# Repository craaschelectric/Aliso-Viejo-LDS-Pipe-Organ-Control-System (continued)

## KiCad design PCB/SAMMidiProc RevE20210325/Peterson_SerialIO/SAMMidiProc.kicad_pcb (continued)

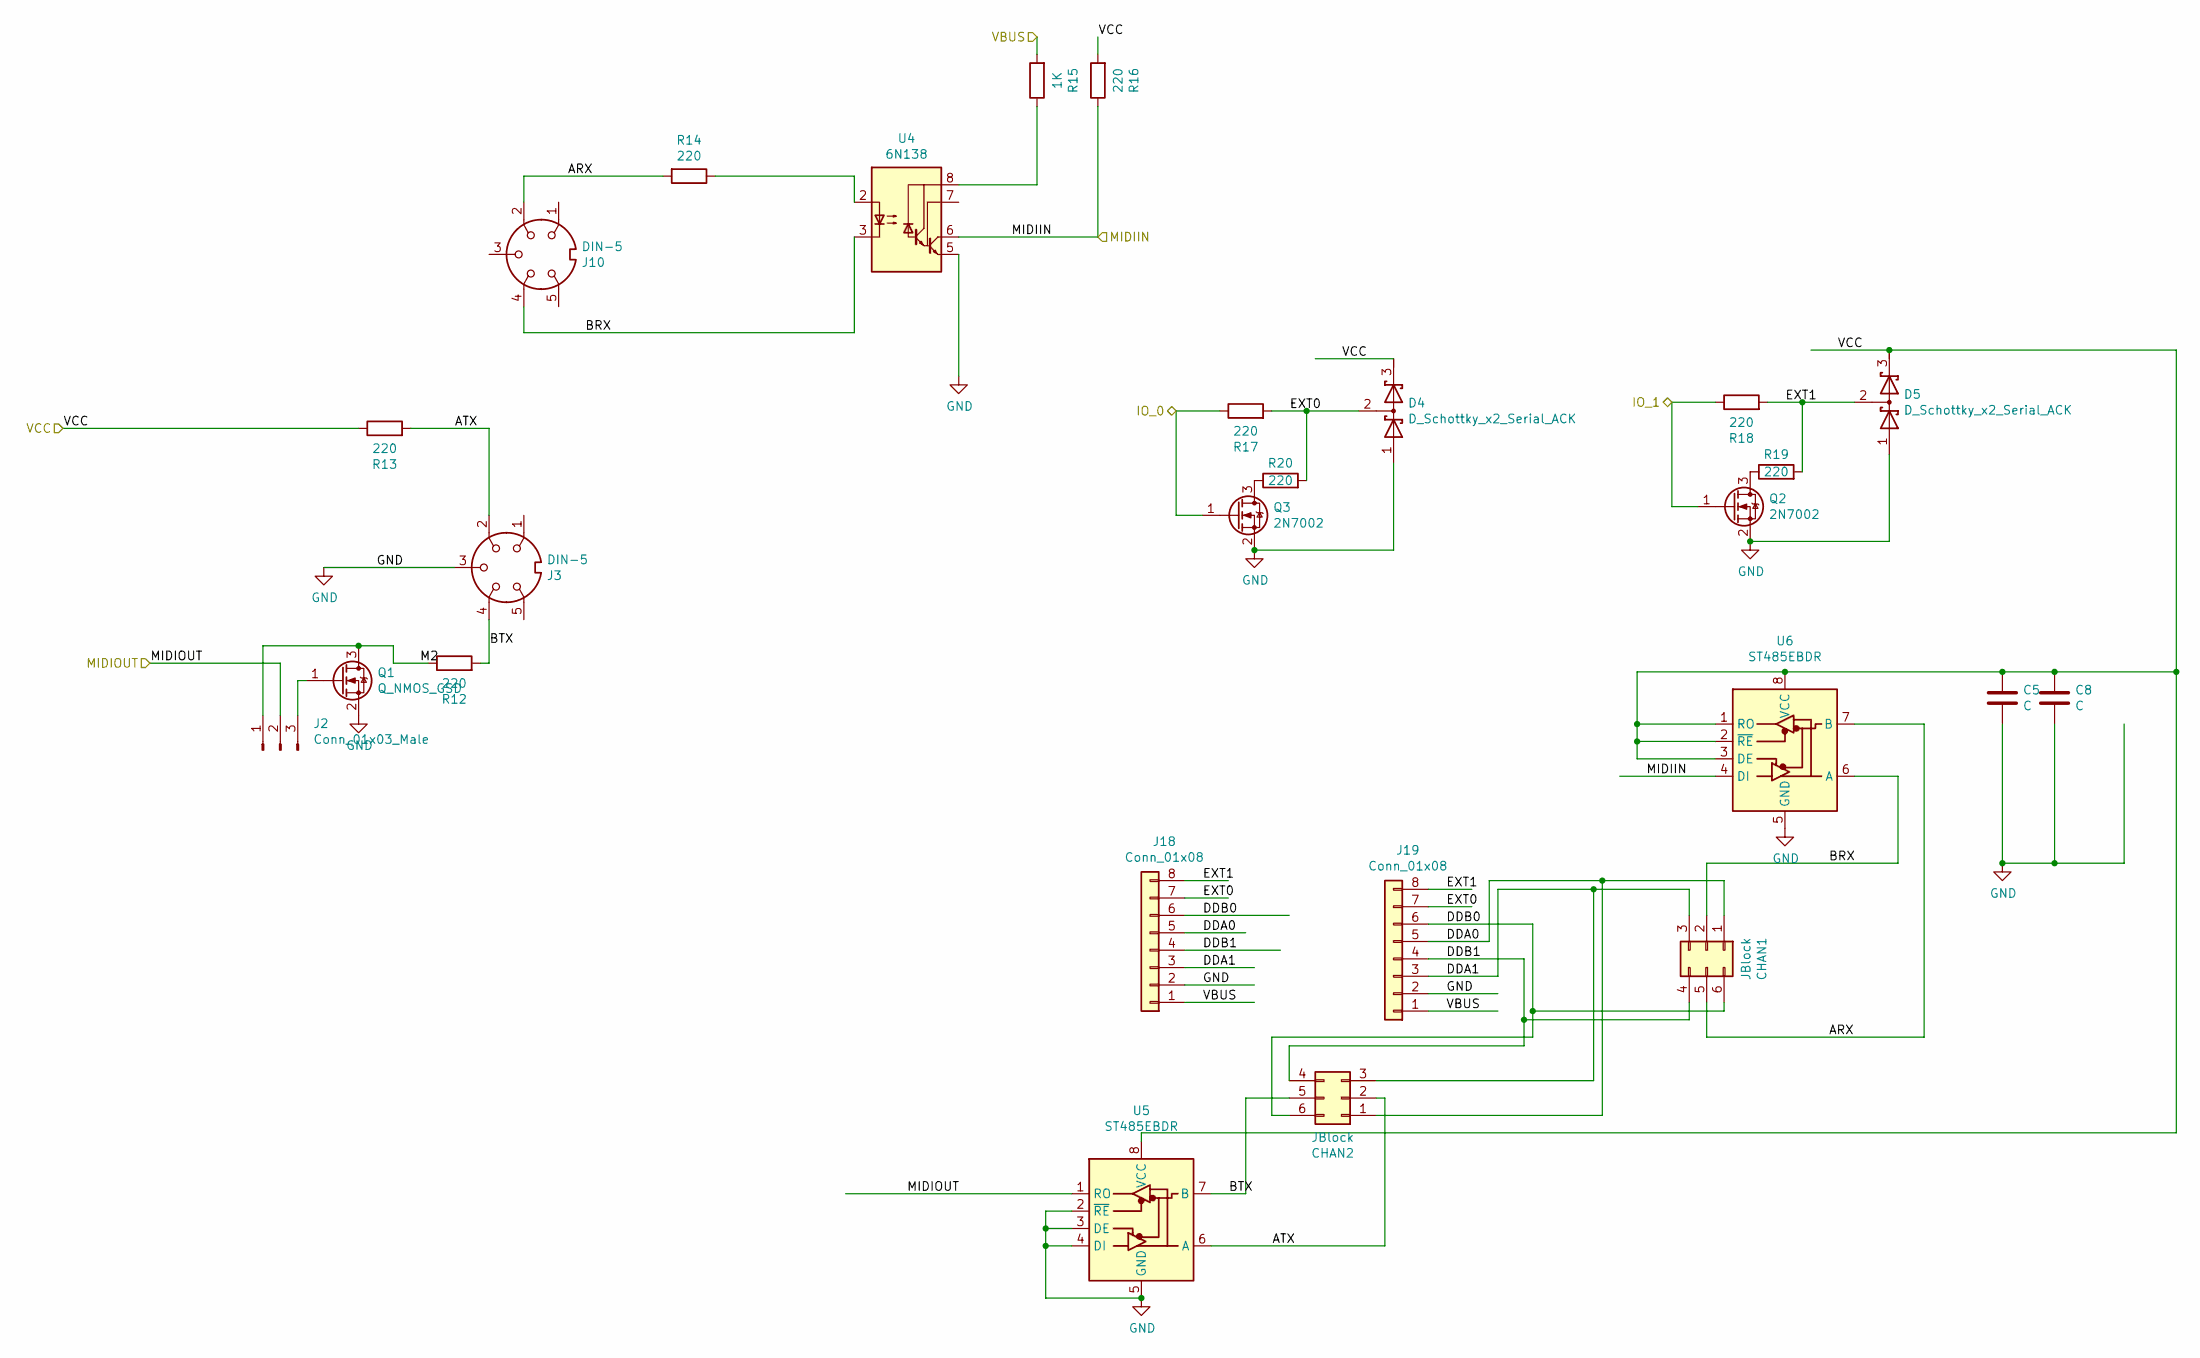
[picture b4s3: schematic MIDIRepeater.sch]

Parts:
C5, C8: C; C_0805_2012Metric_Pad1.18x1.45mm_HandSolder
CHAN1, CHAN2: JBlock; H2X3-2.54
D4, D5: D_Schottky_x2_Serial_ACK; SOT-23_Handsoldering
J2: Conn_01x03_Male; H3-2.54
J3, J10: DIN-5; DIN5_KCDX-5S-S2
J18, J19: Conn_01x08; PinSocket_1x08_P2.54mm_Vertical
Q1: Q_NMOS_GSD; SOT-23_Handsoldering
Q2, Q3: 2N7002; SOT-23_Handsoldering
R12, R13, R14, R16, R17, R18, R19, R20: 220; R_0603_1608Metric_Pad0.98x0.95mm_HandSolder
R15: 1K; R_0603_1608Metric_Pad0.98x0.95mm_HandSolder
U4: 6N138; DIP-8_W7.62mm
U5, U6: ST485EBDR; SOIC-8_3.9x4.9mm_P1.27mm

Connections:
/AN5: Q2.1 (G), R18.1; also elsewhere on the board
/D23: Q3.1 (G), R17.1; also elsewhere on the board
/MIDIPorts/ARX: CHAN1.5, J10.2, R14.2, U6.7 (B)
/MIDIPorts/ATX: CHAN2.2, J3.2, R13.2, U5.6 (A)
/MIDIPorts/BRX: CHAN1.2, J10.4, U4.3 (C2), U6.6 (A)
/MIDIPorts/BTX: CHAN2.5, J3.4, R12.2, U5.7 (B)
/MIDIPorts/DDA0: CHAN1.1, CHAN2.1, J18.5, J19.5
/MIDIPorts/DDA1: CHAN1.3, CHAN2.3, J18.3, J19.3
/MIDIPorts/DDB0: CHAN1.6, CHAN2.6, J18.6, J19.6
/MIDIPorts/DDB1: CHAN1.4, CHAN2.4, J18.4, J19.4
/MIDIPorts/EXT0: D4.2 (common), J18.7, J19.7, R17.2, R20.2
/MIDIPorts/EXT1: D5.2 (common), J18.8, J19.8, R18.2, R19.2
/MIDIPorts/M2: J2.1, Q1.3 (D), R12.1
/MISO: J2.2, U5.1 (RO); also elsewhere on the board
/MOSI: R16.1, U4.6 (VO2), U6.4 (DI); also elsewhere on the board
/VBUS: J18.1, J19.1, R15.2; also elsewhere on the board
GND: C5.2, C8.2, D4.1 (A), D5.1 (A), J3.3, J18.2, J19.2, Q1.2 (S), Q2.2 (S), Q3.2 (S), U4.5 (GND), U5.2 (~RE), U5.3 (DE), U5.4 (DI), U5.5 (GND), U6.5 (GND); also elsewhere on the board
unnamed: J2.3, Q1.1 (G)
unnamed: Q2.3 (D), R19.1
unnamed: Q3.3 (D), R20.1
unnamed: R14.1, U4.2 (C1)
unnamed: R15.1, U4.8 (VCC)
VCC: C5.1, C8.1, D4.3 (K), D5.3 (K), R13.1, R16.2, U5.8 (VCC), U6.1 (RO), U6.2 (~RE), U6.3 (DE), U6.8 (VCC); also elsewhere on the board

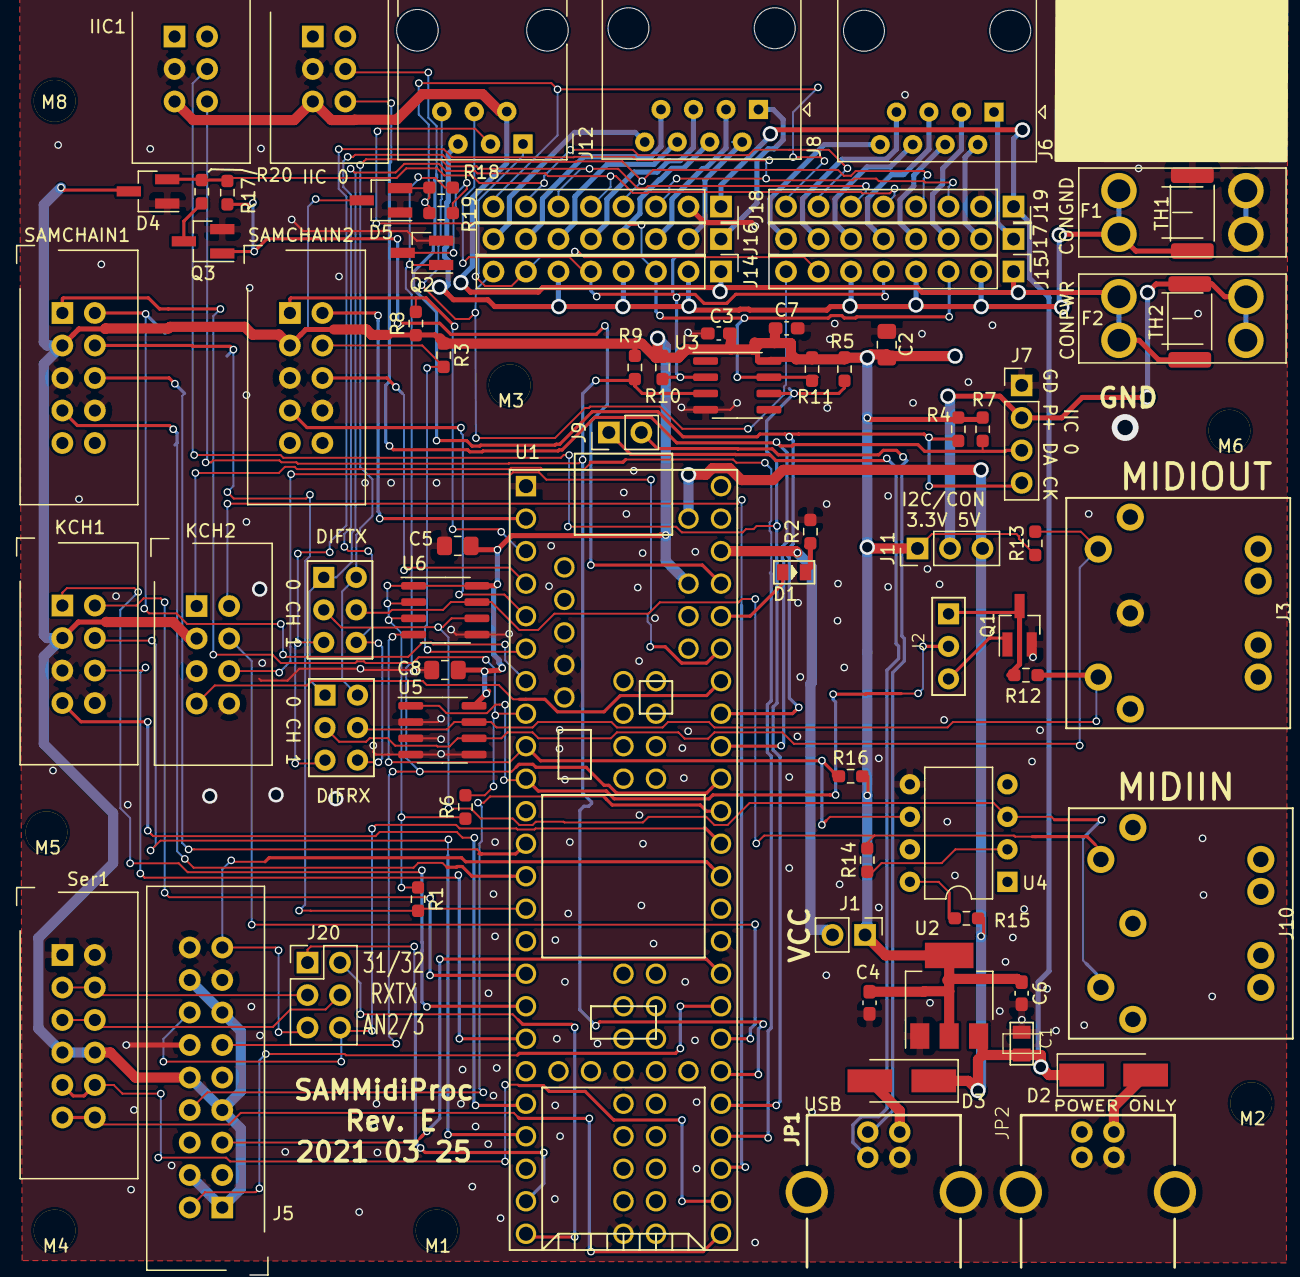
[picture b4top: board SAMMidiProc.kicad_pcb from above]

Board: 2 copper layers, 83 parts (0 on the bottom side), 88 nets.

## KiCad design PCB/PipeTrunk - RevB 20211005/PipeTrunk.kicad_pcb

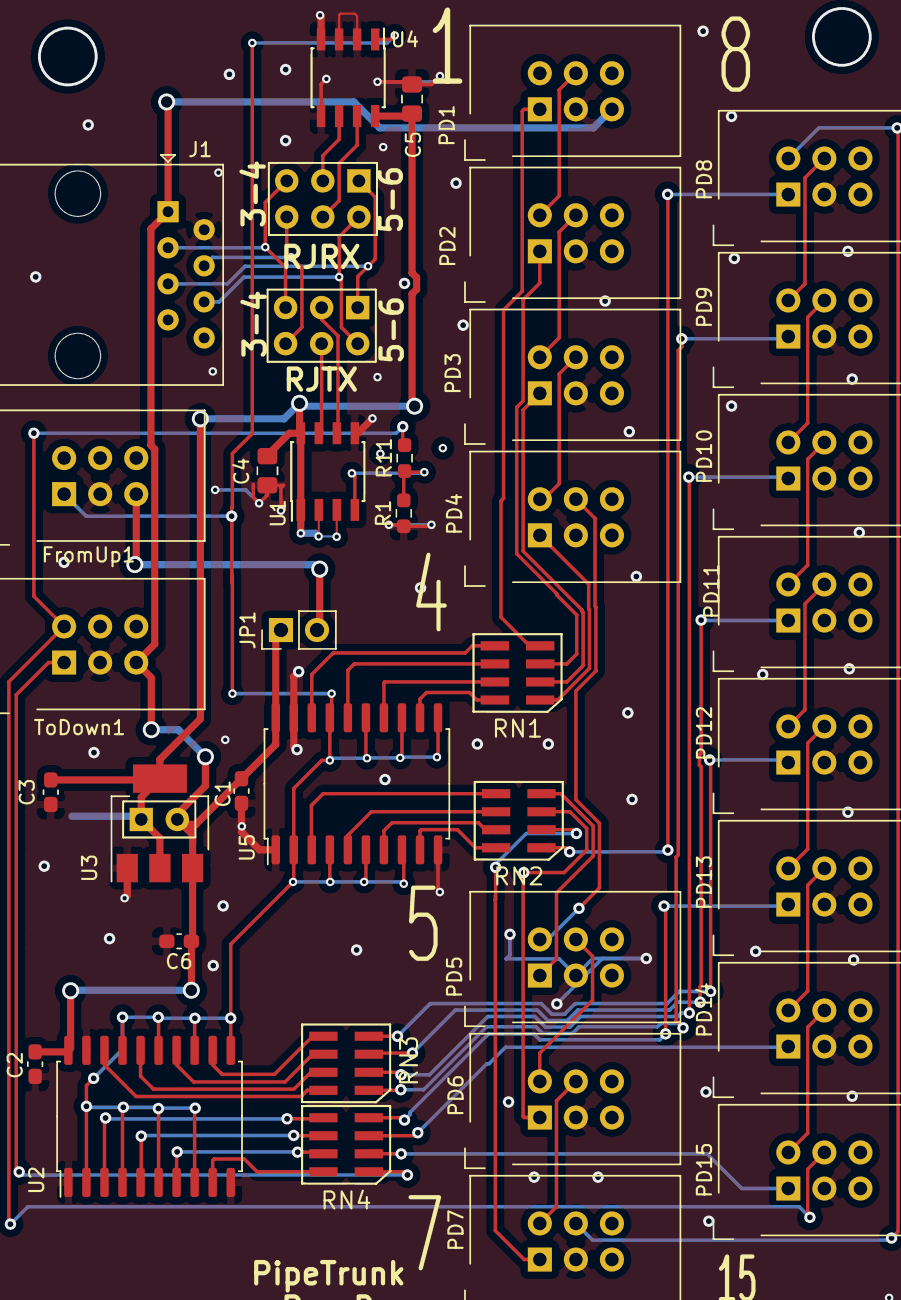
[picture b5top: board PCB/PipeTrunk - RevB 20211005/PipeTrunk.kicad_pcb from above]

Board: 2 copper layers, 39 parts (0 on the bottom side), 61 nets.

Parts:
C1, C2, C3, C6: C; C_0603_1608Metric_Pad1.08x0.95mm_HandSolder
C4, C5: C; C_0805_2012Metric_Pad1.15x1.40mm_HandSolder
CHAN1, CHAN2: JBlock; H2X3-2.54
FromUp1: Conn_02x03_Odd_Even; RibbonCableSocket_6_OddEven
J1: RJ45; RJ45_Amphenol_54602-x08_Horizontal
J2: Conn_01x02_Male; H2-2.54
JP1: Jumper_NC_Small; PinHeader_1x02_P2.54mm_Vertical
PD1, PD2, PD3, PD4, PD5, PD6, PD7, PD8, PD9, PD10, PD11, PD12, PD13, PD14, PD15: Conn_02x03_Odd_Even; RibbonCableSocket_6_OddEven
R1: 330; R_0603_1608Metric_Pad0.98x0.95mm_HandSolder
R11: 220; R_0603_1608Metric_Pad0.98x0.95mm_HandSolder
RN1, RN2, RN3, RN4: R_Pack04; 2012-8
ToDown1: Conn_02x03_Odd_Even; RibbonCableSocket_6_OddEven
U1, U4: ST485EBDR; SOIC-8_3.9x4.9mm_P1.27mm
U2, U5: 74HC244; SOIC-20W_7.5x12.8mm_P1.27mm
U3: AP1117-33; SOT-223-3_TabPin2

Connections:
/3V3: C3.1, C4.1, C5.1, J2.1, U1.1, U1.2, U1.3, U1.8, U3.2, U4.8
/5V: C1.1, C2.1, C6.1, J1.1, J2.2, JP1.1, PD1.5, ToDown1.5, U2.20, U3.3, U5.20
/Ch0RxIn: PD8.4, PD9.2
/Ch1RxIn: PD15.4, R11.2, ToDown1.2
/SysTx0: PD1.1, RN1.4
/SysTx1: PD2.1, RN1.3
/SysTx2: PD3.1, RN1.2
/SysTx3: PD4.1, RN1.1
/SysTx4: PD5.1, RN2.4
/SysTx5: PD6.1, RN2.3
/SysTx6: PD7.1, RN2.2
/SysTx7: PD8.1, RN2.1
/SysTx8: PD9.1, RN3.1
/SysTx9: PD10.1, RN3.2
/SysTx10: PD11.1, RN3.3
/SysTx11: PD12.1, RN3.4
/SysTx12: PD13.1, RN4.4
/SysTx13: PD14.1, RN4.3
/SysTx14: PD15.1, RN4.2
/SysTx15: RN4.1, ToDown1.1
GND: C1.2, C2.2, C3.2, C4.2, C5.2, C6.2, FromUp1.3, J1.2, PD1.3, PD2.3, PD3.3, PD4.3, PD5.3, PD6.3, PD7.3, PD8.3, PD9.3, PD10.3, PD11.3, PD12.3, PD13.3, PD14.3, PD15.3, R1.1, ToDown1.3, U1.5, U2.1, U2.10, U2.19, U3.1, U4.2, U4.3, U4.4, U4.5, U5.1, U5.10, U5.19
unnamed: CHAN1.1, CHAN2.1, J1.5
unnamed: CHAN1.2, U1.6
unnamed: CHAN1.3, CHAN2.3, J1.3
unnamed: CHAN1.4, CHAN2.4, J1.4
unnamed: CHAN1.5, U1.7
unnamed: CHAN1.6, CHAN2.6, J1.6
unnamed: CHAN2.2, U4.6
unnamed: CHAN2.5, U4.7
unnamed: FromUp1.1, U2.2, U2.4, U2.6, U2.8, U2.11, U2.13, U2.15, U2.17, U4.1, U5.2, U5.4, U5.6, U5.8, U5.11, U5.13, U5.15, U5.17
unnamed: FromUp1.5, JP1.2
unnamed: PD1.4, PD2.2
unnamed: PD2.4, PD3.2
unnamed: PD3.4, PD4.2
unnamed: PD4.4, PD5.2
unnamed: PD5.4, PD6.2
unnamed: PD6.4, PD7.2
unnamed: PD7.4, PD8.2
unnamed: PD9.4, PD10.2
unnamed: PD10.4, PD11.2
unnamed: PD11.4, PD12.2
unnamed: PD12.4, PD13.2
unnamed: PD13.4, PD14.2
unnamed: PD14.4, PD15.2
unnamed: R1.2, R11.1, U1.4
unnamed: RN1.5, U5.18
unnamed: RN1.6, U5.16
unnamed: RN1.7, U5.14
unnamed: RN1.8, U5.12
unnamed: RN2.5, U5.3
unnamed: RN2.6, U5.5
unnamed: RN2.7, U5.7
unnamed: RN2.8, U5.9
unnamed: RN3.5, U2.12
unnamed: RN3.6, U2.14
unnamed: RN3.7, U2.16
unnamed: RN3.8, U2.18
unnamed: RN4.5, U2.3
unnamed: RN4.6, U2.5
unnamed: RN4.7, U2.7
unnamed: RN4.8, U2.9

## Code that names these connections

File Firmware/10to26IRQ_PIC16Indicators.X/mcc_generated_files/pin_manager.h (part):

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// get/set IO_RA0 aliases
#define IO_RA0_TRIS                 TRISAbits.TRISA0
#define IO_RA0_LAT                  LATAbits.LATA0
#define IO_RA0_PORT                 PORTAbits.RA0
#define IO_RA0_WPU                  WPUAbits.WPUA0
#define IO_RA0_OD                   ODCONAbits.ODCA0
#define IO_RA0_ANS                  ANSELAbits.ANSA0
#define IO_RA0_SetHigh()            do { LATAbits.LATA0 = 1; } while(0)
#define IO_RA0_SetLow()             do { LATAbits.LATA0 = 0; } while(0)
#define IO_RA0_Toggle()             do { LATAbits.LATA0 = ~LATAbits.LATA0; } while(0)
#define IO_RA0_GetValue()           PORTAbits.RA0
#define IO_RA0_SetDigitalInput()    do { TRISAbits.TRISA0 = 1; } while(0)
#define IO_RA0_SetDigitalOutput()   do { TRISAbits.TRISA0 = 0; } while(0)
#define IO_RA0_SetPullup()          do { WPUAbits.WPUA0 = 1; } while(0)
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// get/set IO_RA1 aliases
#define IO_RA1_TRIS                 TRISAbits.TRISA1
#define IO_RA1_LAT                  LATAbits.LATA1
#define IO_RA1_PORT                 PORTAbits.RA1
#define IO_RA1_WPU                  WPUAbits.WPUA1
#define IO_RA1_OD                   ODCONAbits.ODCA1
#define IO_RA1_ANS                  ANSELAbits.ANSA1
#define IO_RA1_SetHigh()            do { LATAbits.LATA1 = 1; } while(0)
#define IO_RA1_SetLow()             do { LATAbits.LATA1 = 0; } while(0)
#define IO_RA1_Toggle()             do { LATAbits.LATA1 = ~LATAbits.LATA1; } while(0)
#define IO_RA1_GetValue()           PORTAbits.RA1
#define IO_RA1_SetDigitalInput()    do { TRISAbits.TRISA1 = 1; } while(0)
#define IO_RA1_SetDigitalOutput()   do { TRISAbits.TRISA1 = 0; } while(0)
#define IO_RA1_SetPullup()          do { WPUAbits.WPUA1 = 1; } while(0)
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// get/set IO_RA2 aliases
#define IO_RA2_TRIS                 TRISAbits.TRISA2
#define IO_RA2_LAT                  LATAbits.LATA2
#define IO_RA2_PORT                 PORTAbits.RA2
#define IO_RA2_WPU                  WPUAbits.WPUA2
#define IO_RA2_OD                   ODCONAbits.ODCA2
#define IO_RA2_ANS                  ANSELAbits.ANSA2
#define IO_RA2_SetHigh()            do { LATAbits.LATA2 = 1; } while(0)
#define IO_RA2_SetLow()             do { LATAbits.LATA2 = 0; } while(0)
#define IO_RA2_Toggle()             do { LATAbits.LATA2 = ~LATAbits.LATA2; } while(0)
#define IO_RA2_GetValue()           PORTAbits.RA2
#define IO_RA2_SetDigitalInput()    do { TRISAbits.TRISA2 = 1; } while(0)
#define IO_RA2_SetDigitalOutput()   do { TRISAbits.TRISA2 = 0; } while(0)
#define IO_RA2_SetPullup()          do { WPUAbits.WPUA2 = 1; } while(0)
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// get/set IO_RA3 aliases
#define IO_RA3_TRIS                 TRISAbits.TRISA3
#define IO_RA3_LAT                  LATAbits.LATA3
#define IO_RA3_PORT                 PORTAbits.RA3
#define IO_RA3_WPU                  WPUAbits.WPUA3
#define IO_RA3_OD                   ODCONAbits.ODCA3
#define IO_RA3_ANS                  ANSELAbits.ANSA3
#define IO_RA3_SetHigh()            do { LATAbits.LATA3 = 1; } while(0)
#define IO_RA3_SetLow()             do { LATAbits.LATA3 = 0; } while(0)
#define IO_RA3_Toggle()             do { LATAbits.LATA3 = ~LATAbits.LATA3; } while(0)
#define IO_RA3_GetValue()           PORTAbits.RA3
#define IO_RA3_SetDigitalInput()    do { TRISAbits.TRISA3 = 1; } while(0)
#define IO_RA3_SetDigitalOutput()   do { TRISAbits.TRISA3 = 0; } while(0)
#define IO_RA3_SetPullup()          do { WPUAbits.WPUA3 = 1; } while(0)
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// get/set IO_RA4 aliases
#define IO_RA4_TRIS                 TRISAbits.TRISA4
#define IO_RA4_LAT                  LATAbits.LATA4
#define IO_RA4_PORT                 PORTAbits.RA4
#define IO_RA4_WPU                  WPUAbits.WPUA4
#define IO_RA4_OD                   ODCONAbits.ODCA4
#define IO_RA4_ANS                  ANSELAbits.ANSA4
#define IO_RA4_SetHigh()            do { LATAbits.LATA4 = 1; } while(0)
#define IO_RA4_SetLow()             do { LATAbits.LATA4 = 0; } while(0)
#define IO_RA4_Toggle()             do { LATAbits.LATA4 = ~LATAbits.LATA4; } while(0)
#define IO_RA4_GetValue()           PORTAbits.RA4
#define IO_RA4_SetDigitalInput()    do { TRISAbits.TRISA4 = 1; } while(0)
#define IO_RA4_SetDigitalOutput()   do { TRISAbits.TRISA4 = 0; } while(0)
#define IO_RA4_SetPullup()          do { WPUAbits.WPUA4 = 1; } while(0)
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// get/set IO_RA5 aliases
#define IO_RA5_TRIS                 TRISAbits.TRISA5
#define IO_RA5_LAT                  LATAbits.LATA5
#define IO_RA5_PORT                 PORTAbits.RA5
#define IO_RA5_WPU                  WPUAbits.WPUA5
#define IO_RA5_OD                   ODCONAbits.ODCA5
#define IO_RA5_ANS                  ANSELAbits.ANSA5
#define IO_RA5_SetHigh()            do { LATAbits.LATA5 = 1; } while(0)
#define IO_RA5_SetLow()             do { LATAbits.LATA5 = 0; } while(0)
#define IO_RA5_Toggle()             do { LATAbits.LATA5 = ~LATAbits.LATA5; } while(0)
#define IO_RA5_GetValue()           PORTAbits.RA5
#define IO_RA5_SetDigitalInput()    do { TRISAbits.TRISA5 = 1; } while(0)
#define IO_RA5_SetDigitalOutput()   do { TRISAbits.TRISA5 = 0; } while(0)
#define IO_RA5_SetPullup()          do { WPUAbits.WPUA5 = 1; } while(0)
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// get/set IO_RA6 aliases
#define IO_RA6_TRIS                 TRISAbits.TRISA6
#define IO_RA6_LAT                  LATAbits.LATA6
#define IO_RA6_PORT                 PORTAbits.RA6
#define IO_RA6_WPU                  WPUAbits.WPUA6
#define IO_RA6_OD                   ODCONAbits.ODCA6
#define IO_RA6_ANS                  ANSELAbits.ANSA6
#define IO_RA6_SetHigh()            do { LATAbits.LATA6 = 1; } while(0)
#define IO_RA6_SetLow()             do { LATAbits.LATA6 = 0; } while(0)
#define IO_RA6_Toggle()             do { LATAbits.LATA6 = ~LATAbits.LATA6; } while(0)
#define IO_RA6_GetValue()           PORTAbits.RA6
#define IO_RA6_SetDigitalInput()    do { TRISAbits.TRISA6 = 1; } while(0)
#define IO_RA6_SetDigitalOutput()   do { TRISAbits.TRISA6 = 0; } while(0)
#define IO_RA6_SetPullup()          do { WPUAbits.WPUA6 = 1; } while(0)
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// get/set IO_RA7 aliases
#define IO_RA7_TRIS                 TRISAbits.TRISA7
#define IO_RA7_LAT                  LATAbits.LATA7
#define IO_RA7_PORT                 PORTAbits.RA7
#define IO_RA7_WPU                  WPUAbits.WPUA7
#define IO_RA7_OD                   ODCONAbits.ODCA7
#define IO_RA7_ANS                  ANSELAbits.ANSA7
#define IO_RA7_SetHigh()            do { LATAbits.LATA7 = 1; } while(0)
#define IO_RA7_SetLow()             do { LATAbits.LATA7 = 0; } while(0)
#define IO_RA7_Toggle()             do { LATAbits.LATA7 = ~LATAbits.LATA7; } while(0)
#define IO_RA7_GetValue()           PORTAbits.RA7
#define IO_RA7_SetDigitalInput()    do { TRISAbits.TRISA7 = 1; } while(0)
#define IO_RA7_SetDigitalOutput()   do { TRISAbits.TRISA7 = 0; } while(0)
#define IO_RA7_SetPullup()          do { WPUAbits.WPUA7 = 1; } while(0)
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// get/set SYNC aliases
#define SYNC_TRIS                 TRISBbits.TRISB2
#define SYNC_LAT                  LATBbits.LATB2
#define SYNC_PORT                 PORTBbits.RB2
#define SYNC_WPU                  WPUBbits.WPUB2
#define SYNC_OD                   ODCONBbits.ODCB2
#define SYNC_ANS                  ANSELBbits.ANSB2
#define SYNC_SetHigh()            do { LATBbits.LATB2 = 1; } while(0)
#define SYNC_SetLow()             do { LATBbits.LATB2 = 0; } while(0)
#define SYNC_Toggle()             do { LATBbits.LATB2 = ~LATBbits.LATB2; } while(0)
#define SYNC_GetValue()           PORTBbits.RB2
#define SYNC_SetDigitalInput()    do { TRISBbits.TRISB2 = 1; } while(0)
#define SYNC_SetDigitalOutput()   do { TRISBbits.TRISB2 = 0; } while(0)
#define SYNC_SetPullup()          do { WPUBbits.WPUB2 = 1; } while(0)
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// get/set MASTEROUT aliases
#define MASTEROUT_TRIS                 TRISBbits.TRISB3
#define MASTEROUT_LAT                  LATBbits.LATB3
#define MASTEROUT_PORT                 PORTBbits.RB3
#define MASTEROUT_WPU                  WPUBbits.WPUB3
#define MASTEROUT_OD                   ODCONBbits.ODCB3
#define MASTEROUT_ANS                  ANSELBbits.ANSB3
#define MASTEROUT_SetHigh()            do { LATBbits.LATB3 = 1; } while(0)
#define MASTEROUT_SetLow()             do { LATBbits.LATB3 = 0; } while(0)
#define MASTEROUT_Toggle()             do { LATBbits.LATB3 = ~LATBbits.LATB3; } while(0)
#define MASTEROUT_GetValue()           PORTBbits.RB3
#define MASTEROUT_SetDigitalInput()    do { TRISBbits.TRISB3 = 1; } while(0)
#define MASTEROUT_SetDigitalOutput()   do { TRISBbits.TRISB3 = 0; } while(0)
#define MASTEROUT_SetPullup()          do { WPUBbits.WPUB3 = 1; } while(0)
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// get/set PERIPHOUT aliases
#define PERIPHOUT_TRIS                 TRISBbits.TRISB4
#define PERIPHOUT_LAT                  LATBbits.LATB4
#define PERIPHOUT_PORT                 PORTBbits.RB4
#define PERIPHOUT_WPU                  WPUBbits.WPUB4
#define PERIPHOUT_OD                   ODCONBbits.ODCB4
#define PERIPHOUT_ANS                  ANSELBbits.ANSB4
#define PERIPHOUT_SetHigh()            do { LATBbits.LATB4 = 1; } while(0)
#define PERIPHOUT_SetLow()             do { LATBbits.LATB4 = 0; } while(0)
#define PERIPHOUT_Toggle()             do { LATBbits.LATB4 = ~LATBbits.LATB4; } while(0)
#define PERIPHOUT_GetValue()           PORTBbits.RB4
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
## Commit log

2025-12-26 Initial commit: Pipe organ control system for Aliso Viejo, CA LDS church. Wicks conversion.
2025-12-27 adding pipe map spreadsheet to docs
